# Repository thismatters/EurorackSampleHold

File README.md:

# Noise / Sample Hold

This module both generates random noise (white and pink) which can be used as an audio signal directly, or slow moving random voltages appropriate to use a CV. Additionally, it can sample that random noise and hold a CV (slash V/Oct). Module has an internal clock to control sample rate, which can be overridden.

The circuit here is based on the [Yusynth Random Module](https://yusynth.net/Modular/EN/NOISE/index.html) with minor tweaks to make it more Eurorack friendly. The changes I've made are thus:
* Selected resistors appropriate for +/-12V rails,
* Added polarity protection so that a backward power header doesn't fry anything (twin series schotty diodes: BAT54SL),
* Full surface mount design.

The Yusynth page is a treasure trove of information about this circuit that I am too amateur to claim as my own; please read that outstanding page before using this circuit. The page provides many details and other implementations of this circuit that you may find suitable.

The KiCAD project here uses the library/footprints [found in my companion repo](https://github.com/thismatters/EurorackKiCAD).

## Width

13hp on an Intellijel 1U rack.

## Inputs

Jacks for:
- Signal to be sampled,
- Gate controlling when sample is taken.

Switch for selecting between noise:
- White,
- Pink,
- Slow moving random voltage.

Knob for setting internal clock for sample rate.

## Outputs

Jacks for:
- Selected noise,
- Clock,
- Held voltage.

## Adjustment

Build this module using a socket for the discrete transistor. Try several transistors until you get a good spectrum of both white and pink noise.

## Vendors

There are part numbers in the [BOM](.csv) for many of the parts (not for basic passives though) at the following vendors:

* [Mouser](https://www.mouser.com): Needs no introduction. Get your ICs from here (or [digikey](https://www.digikey.com)).
* [Tayda Electronics](https://www.taydaelectronics.com/): Good supplier for passive components; audio jacks, and potentiometers. Their audio jacks are slightly smaller than the thonkiconn from thonk.
* [Love My Switches](https://lovemyswitches.com/): Has [really good knobs](https://lovemyswitches.com/anodized-aluminum-knob-the-lo-fi-1-4-smooth-shaft-12-5mm-od/) to go on those potentiometers!
* [OSHPark](https://oshpark.com/): Fast and (relatively) cheap PCB manufacturer. The [V0 circuit](https://oshpark.com/shared_projects/IxCpIOaM) works great!

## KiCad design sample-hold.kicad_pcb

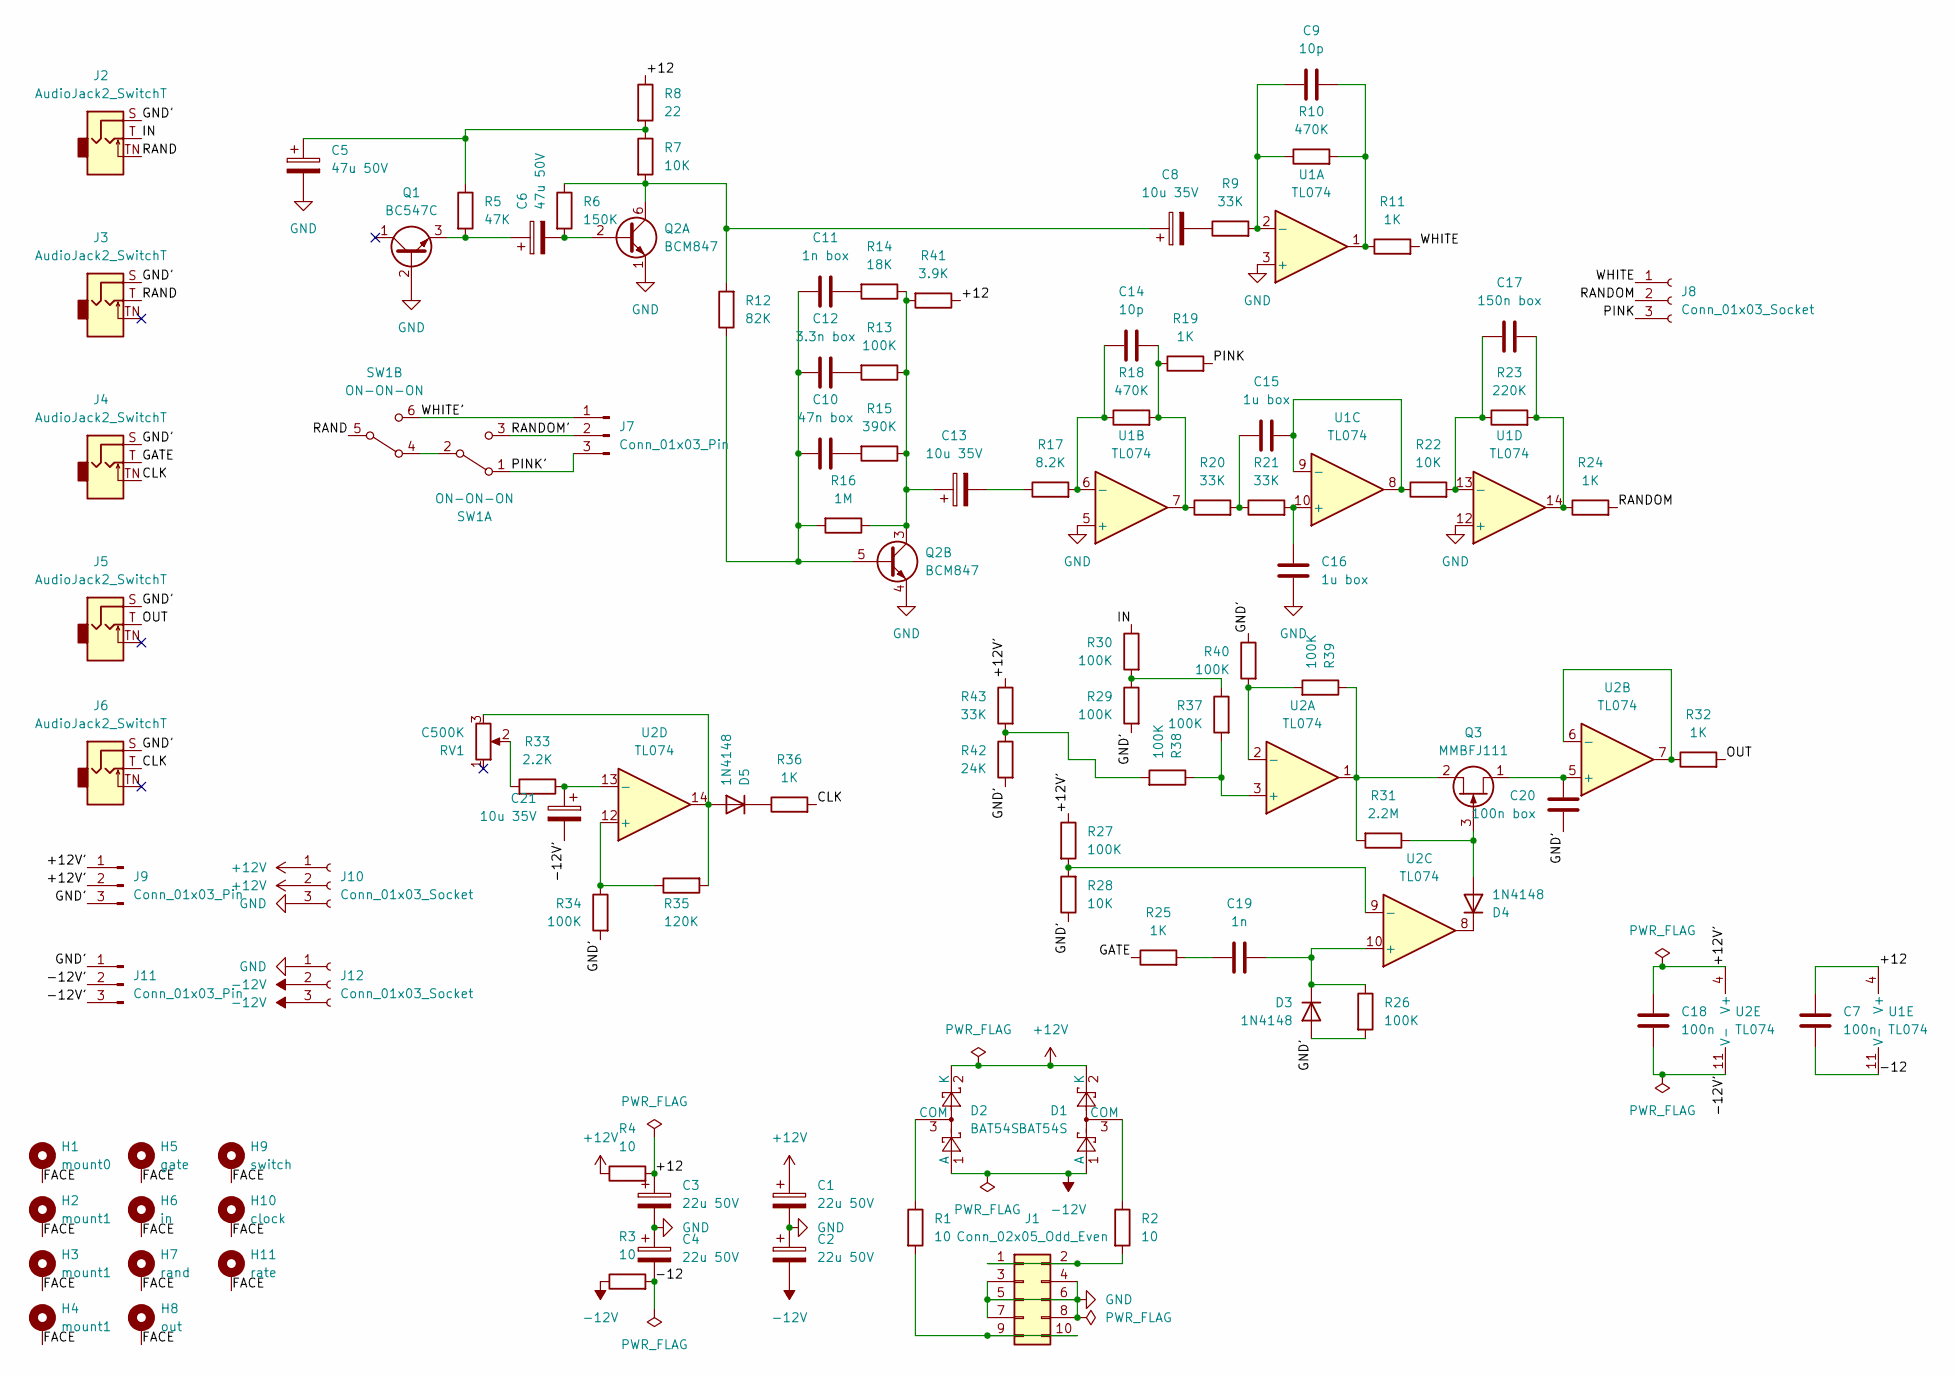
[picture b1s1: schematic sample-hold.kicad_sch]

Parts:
C1, C2, C3, C4: 22u 50V; CP_Radial_D5.0mm_P2.50mm
C5, C6: 47u 50V; CP_Radial_D6.3mm_P2.50mm
C7, C18: 100n; C_0805_2012Metric
C8, C13, C21: 10u 35V; CP_Radial_D5.0mm_P2.50mm
C9, C14: 10p; C_0805_2012Metric
C10: 47n box; C_Rect_L7.2mm_W2.5mm_P5.00mm_FKS2_FKP2_MKS2_MKP2
C11: 1n box; C_Rect_L7.2mm_W2.5mm_P5.00mm_FKS2_FKP2_MKS2_MKP2
C12: 3.3n box; C_Rect_L7.2mm_W2.5mm_P5.00mm_FKS2_FKP2_MKS2_MKP2
C15, C16: 1u box; C_Rect_L7.2mm_W5.5mm_P5.00mm_FKS2_FKP2_MKS2_MKP2
C17: 150n box; C_Rect_L7.2mm_W3.5mm_P5.00mm_FKS2_FKP2_MKS2_MKP2
C19: 1n; C_0805_2012Metric
C20: 100n box; C_Rect_L7.2mm_W2.5mm_P5.00mm_FKS2_FKP2_MKS2_MKP2
D1, D2: BAT54S; SOT-23; PartNum 863-BAT54SLT1G
D3, D4, D5: 1N4148; D_SOD-323_HandSoldering
H1: mount0; Mech-MountingHole
H2, H3, H4: mount1; Mech-MountingHole
H5: gate; Mech-AudioJack-Hole-Input-Gate
H6: in; Mech-AudioJack-Hole-Input-Voct
H7: rand; Mech-AudioJack-Hole-Output-Voct
H8: out; Mech-AudioJack-Hole-Output-Voct
H9: switch; Mech-2M_Switch-Hole
H10: clock; Mech-AudioJack-Hole-Output-Clock
H11: rate; Mech-Potentiometer-Hole_level_90deg
J1: Conn_02x05_Odd_Even; PinHeader_2x05_P2.54mm_Vertical; PartNum A-2939
J2, J3, J4, J5, J6: AudioJack2_SwitchT; AudioJack2_Tayda_A-2566; PartNum A-2566
J7, J9, J11: Conn_01x03_Pin; PinHeader_1x03_P2.54mm_Vertical
J8, J10, J12: Conn_01x03_Socket; PinSocket_1x03_P2.54mm_Vertical
Q1: BC547C; TO-92_Inline_Wide; PartNum 637-BC547C
Q2: BCM847; TSOP-6_1.65x3.05mm_P0.95mm; PartNum 771-BCM847DS135
Q3: MMBFJ111; SOT-23; PartNum 863-MMBF4393LT1G
R1, R2, R3, R4: 10; R_0805_2012Metric
R5: 47K; R_0805_2012Metric
R6: 150K; R_0805_2012Metric
R7, R22, R28: 10K; R_0805_2012Metric
R8: 22; R_0805_2012Metric
R9, R20, R21, R43: 33K; R_0805_2012Metric
R10, R18: 470K; R_0805_2012Metric
R11, R19, R24, R25, R32, R36: 1K; R_0805_2012Metric
R12: 82K; R_0805_2012Metric
R13, R26, R27, R29, R30, R34, R37, R38, R39, R40: 100K; R_0805_2012Metric
R14: 18K; R_0805_2012Metric
R15: 390K; R_0805_2012Metric
R16: 1M; R_0805_2012Metric
R17: 8.2K; R_0805_2012Metric
R23: 220K; R_0805_2012Metric
R31: 2.2M; R_0805_2012Metric
R33: 2.2K; R_0805_2012Metric
R35: 120K; R_0805_2012Metric
R41: 3.9K; R_0805_2012Metric
R42: 24K; R_0805_2012Metric
RV1: C500K; Potentiometer_RV16AF-41-15R1; PartNum A-3940
SW1: ON-ON-ON; Switch_DPDT_Tayda_A-5752; PartNum A-6677
U1, U2: TL074; SOIC-14_3.9x8.7mm_P1.27mm; PartNum 595-TL074CDR

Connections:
+12V: C1.1, D1.2 (K), D2.2 (K), J10.1, J10.2, R4.1
-12V: C2.2, D1.1 (A), D2.1 (A), J12.2, J12.3, R3.1
/+12: C3.1, C7.1, R4.2, R8.1, R41.1, U1.4 (V+)
/+12V': C18.1, J9.1, J9.2, R27.1, R43.1, U2.4 (V+)
/-12: C4.2, C7.2, R3.2, U1.11 (V-)
/-12V': C18.2, C21.2, J11.2, J11.3, U2.11 (V-)
/CLK: J4.TN, J6.T, R36.2
/FACE: H1.1, H2.1, H3.1, H4.1, H5.1, H6.1, H7.1, H8.1, H9.1, H10.1, H11.1
/GATE: J4.T, R25.1
/GND': C20.2, D3.2 (A), J2.S, J3.S, J4.S, J5.S, J6.S, J9.3, J11.1, R26.2, R28.1, R29.2, R34.2, R40.1, R42.2
/IN: J2.T, R30.1
/OUT: J5.T, R32.2
/PINK: J8.3, R19.2
/PINK': J7.3, SW1.1 (A)
/RAND: J2.TN, J3.T, SW1.5 (B)
/RANDOM: J8.2, R24.2
/RANDOM': J7.2, SW1.3 (C)
/WHITE: J8.1, R11.2
/WHITE': J7.1, SW1.6 (C)
GND: C1.2, C2.1, C3.2, C4.1, C5.2, C16.1, J1.3, J1.4, J1.5, J1.6, J1.7, J1.8, J10.3, J12.1, Q1.2 (B), Q2.1 (E1), Q2.4 (E2), U1.3 (+), U1.5 (+), U1.12 (+)
unnamed: C5.1, R5.1, R7.1, R8.2
unnamed: C8.2, R9.1
unnamed: C9.2, R10.2, R11.1, U1.1
unnamed: C10.2, R15.2
unnamed: C11.2, R14.2
unnamed: C12.2, R13.2
unnamed: C13.2, R17.1
unnamed: C14.2, R18.2, R19.1, R20.1, U1.7
unnamed: C15.1, R20.2, R21.1
unnamed: C17.2, R23.2, R24.1, U1.14
unnamed: C19.1, R25.2
unnamed: D1.3 (COM), R2.1
unnamed: D2.3 (COM), R1.1
unnamed: C19.2, D3.1 (K), R26.1, U2.10 (+)
unnamed: D4.2 (A), Q3.3 (G), R31.1
unnamed: D4.1 (K), U2.8
unnamed: D5.2 (A), R35.2, RV1.3, U2.14
unnamed: D5.1 (K), R36.1
unnamed: J1.1, J1.2, R2.2
unnamed: J1.9, J1.10, R1.2
unnamed: C6.1, Q1.3 (E), R5.2
unnamed: C6.2, Q2.2 (B1), R6.2
unnamed: C8.1, Q2.6 (C1), R6.1, R7.2, R12.2
unnamed: C10.1, C11.1, C12.1, Q2.5 (B2), R12.1, R16.2
unnamed: C13.1, Q2.3 (C2), R13.1, R14.1, R15.1, R16.1, R41.2
unnamed: C20.1, Q3.1 (D), U2.5 (+)
unnamed: Q3.2 (S), R31.2, R39.1, U2.1
unnamed: R29.1, R30.2, R37.1
unnamed: R33.2, RV1.2
unnamed: R38.2, R42.1, R43.2
unnamed: SW1.2 (B), SW1.4 (A)
unnamed: C9.1, R9.2, R10.1, U1.2 (-)
unnamed: C14.1, R17.2, R18.1, U1.6 (-)
unnamed: C16.2, R21.2, U1.10 (+)
unnamed: C15.2, R22.1, U1.8, U1.9 (-)
unnamed: C17.1, R22.2, R23.1, U1.13 (-)
unnamed: R37.2, R38.1, U2.3 (+)
unnamed: R39.2, R40.2, U2.2 (-)
unnamed: R32.1, U2.6 (-), U2.7
unnamed: R27.2, R28.2, U2.9 (-)
unnamed: R34.1, R35.1, U2.12 (+)
unnamed: C21.1, R33.1, U2.13 (-)

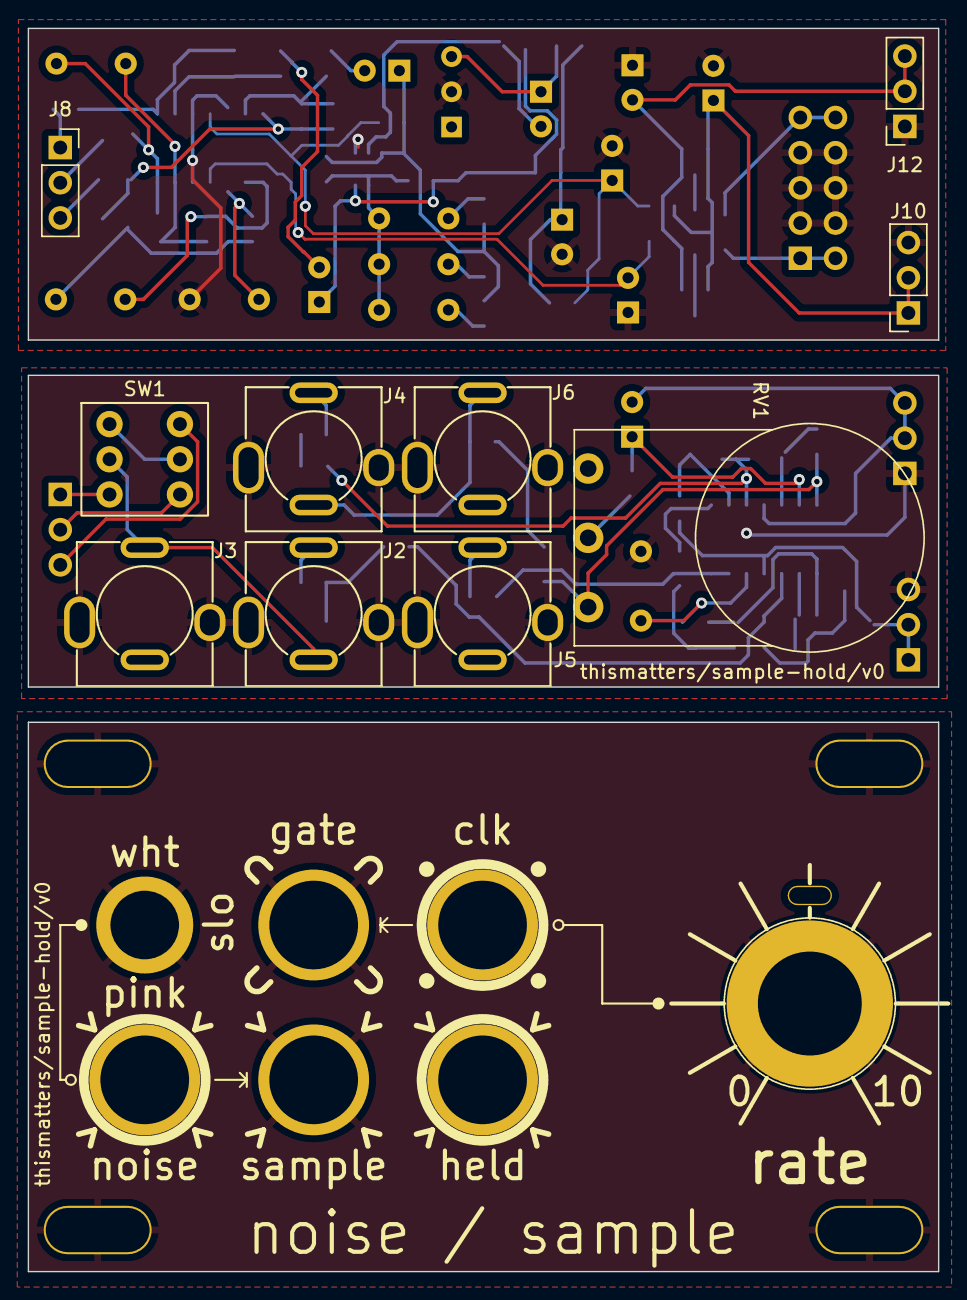
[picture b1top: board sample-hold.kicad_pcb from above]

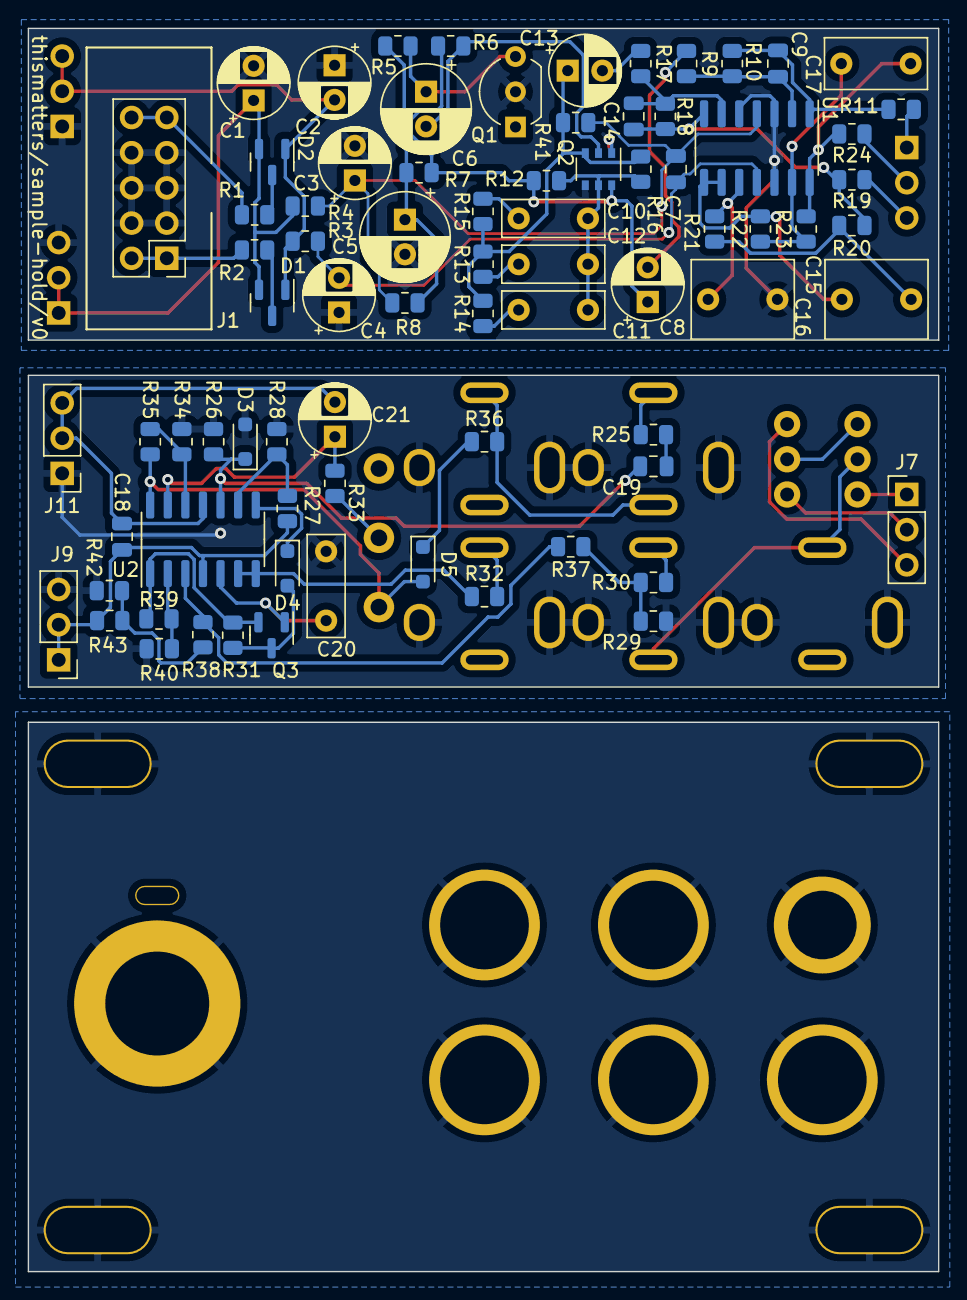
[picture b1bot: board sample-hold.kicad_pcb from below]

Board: 2 copper layers, 65.7 x 89.7 mm, 99 parts (78 on the bottom side), 62 nets.

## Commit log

2024-09-08 adding rate knob and internal clock
2024-09-08 correct capacitor type
2024-09-08 little routing cleanup
2024-11-03 prototype tested and updates made ready for v0 manu
2024-11-17 sent out for manu
2024-11-17 add readme
2024-11-24 adding circuit link
